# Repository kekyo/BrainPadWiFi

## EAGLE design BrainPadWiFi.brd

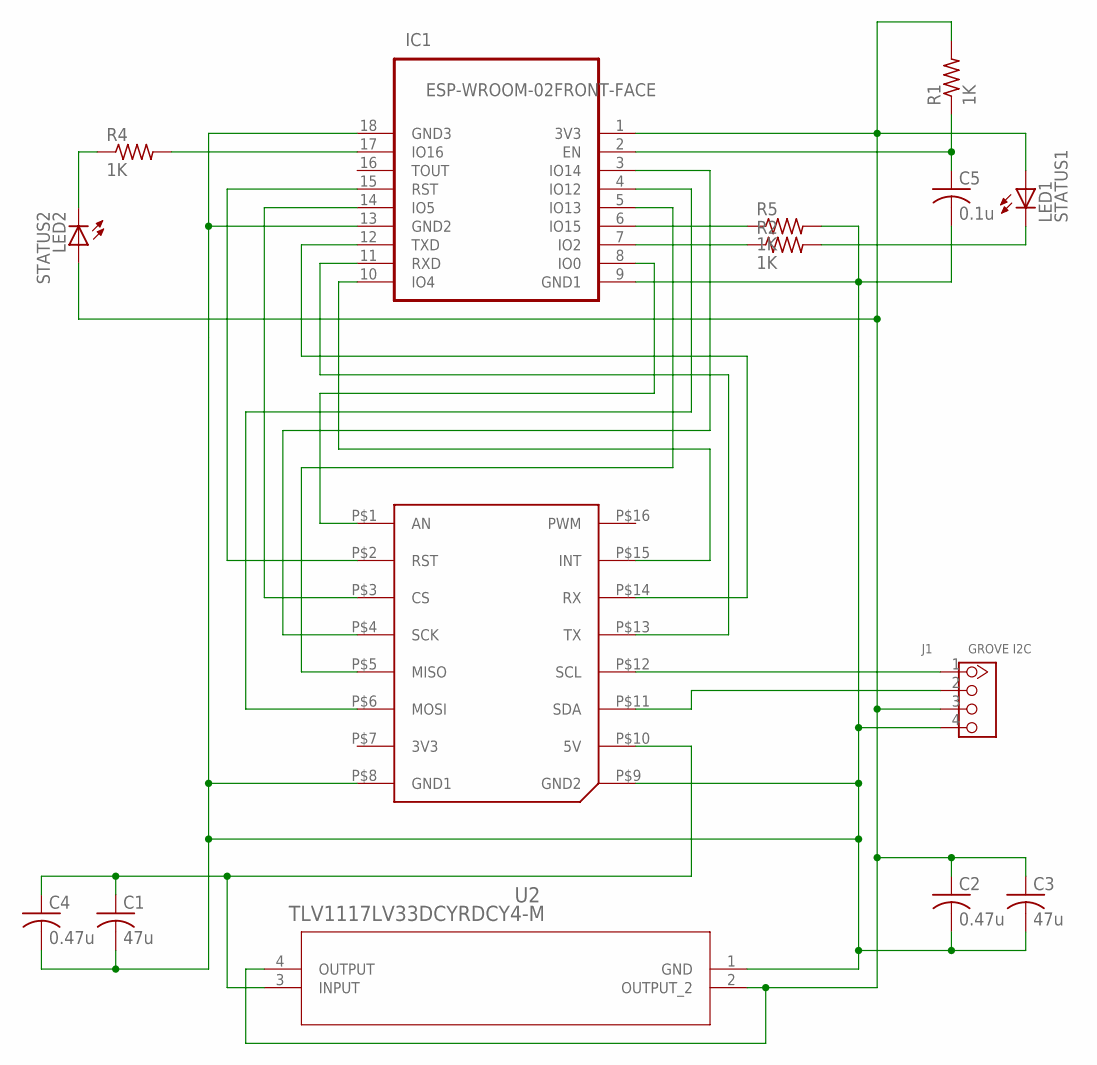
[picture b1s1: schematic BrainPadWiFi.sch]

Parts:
C1, C3: 47u; C1206
C2, C4: 0.47u; C1206
C5: 0.1u; C1206
IC1: ESP-WROOM-02FRONT-FACE; FRONT-FACE
J1: GROVE I2C; HW4-2.0
LED1: STATUS1; SML1206
LED2: STATUS2; SML1206
R1, R2, R4, R5: 1K; R1206
U2: TLV1117LV33DCYRDCY4-M; DCY4-M
U$1: MIKROE_CLICKMINI; MIKROE_BUS_MINI

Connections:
3V3: C2.1, C3.1, IC1.1 (3V3), J1.3, LED1.A, LED2.A, R1.2, U2.2 (OUTPUT_2), U2.4 (OUTPUT)
5V: C1.1, C4.1, U2.3 (INPUT), U$1.P$10 (5V)
CS: IC1.14 (IO5), U$1.P$3 (CS)
EN: C5.1, IC1.2 (EN), R1.1
GND: C1.2, C2.2, C3.2, C4.2, C5.2, IC1.9 (GND1), IC1.13 (GND2), IC1.18 (GND3), J1.4, R5.2, U2.1 (GND), U$1.P$8 (GND1), U$1.P$9 (GND2)
INT: IC1.10 (IO4), U$1.P$15 (INT)
IO2: IC1.7 (IO2), R2.1
IO15: IC1.6 (IO15), R5.1
IO16: IC1.17 (IO16), R4.2
MISO: IC1.5 (IO13), U$1.P$5 (MISO)
MOSI: IC1.4 (IO12), U$1.P$6 (MOSI)
PROG: IC1.8 (IO0), U$1.P$1 (AN)
RST: IC1.15 (RST), U$1.P$2 (RST)
RX: IC1.12 (TXD), U$1.P$14 (RX)
SCK: IC1.3 (IO14), U$1.P$4 (SCK)
SCL: J1.1, U$1.P$12 (SCL)
SDA: J1.2, U$1.P$11 (SDA)
STAT1: LED1.C, R2.2
STAT2: LED2.C, R4.1
TX: IC1.11 (RXD), U$1.P$13 (TX)

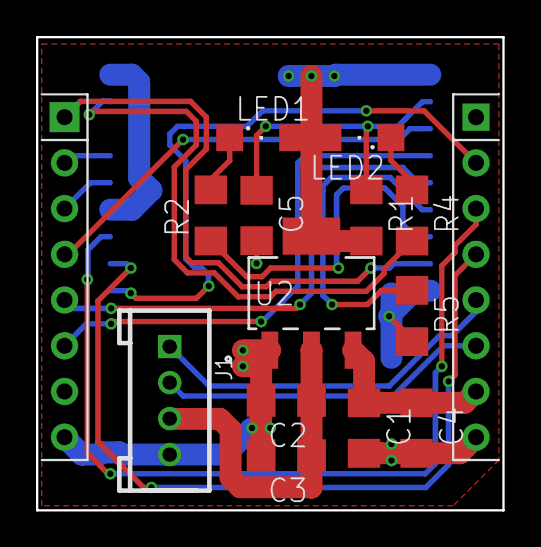
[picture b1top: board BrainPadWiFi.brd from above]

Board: 2 copper layers, 25.9 x 26.3 mm, 16 parts (1 on the bottom side), 20 nets.

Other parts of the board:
U$3: OSH-LOGO

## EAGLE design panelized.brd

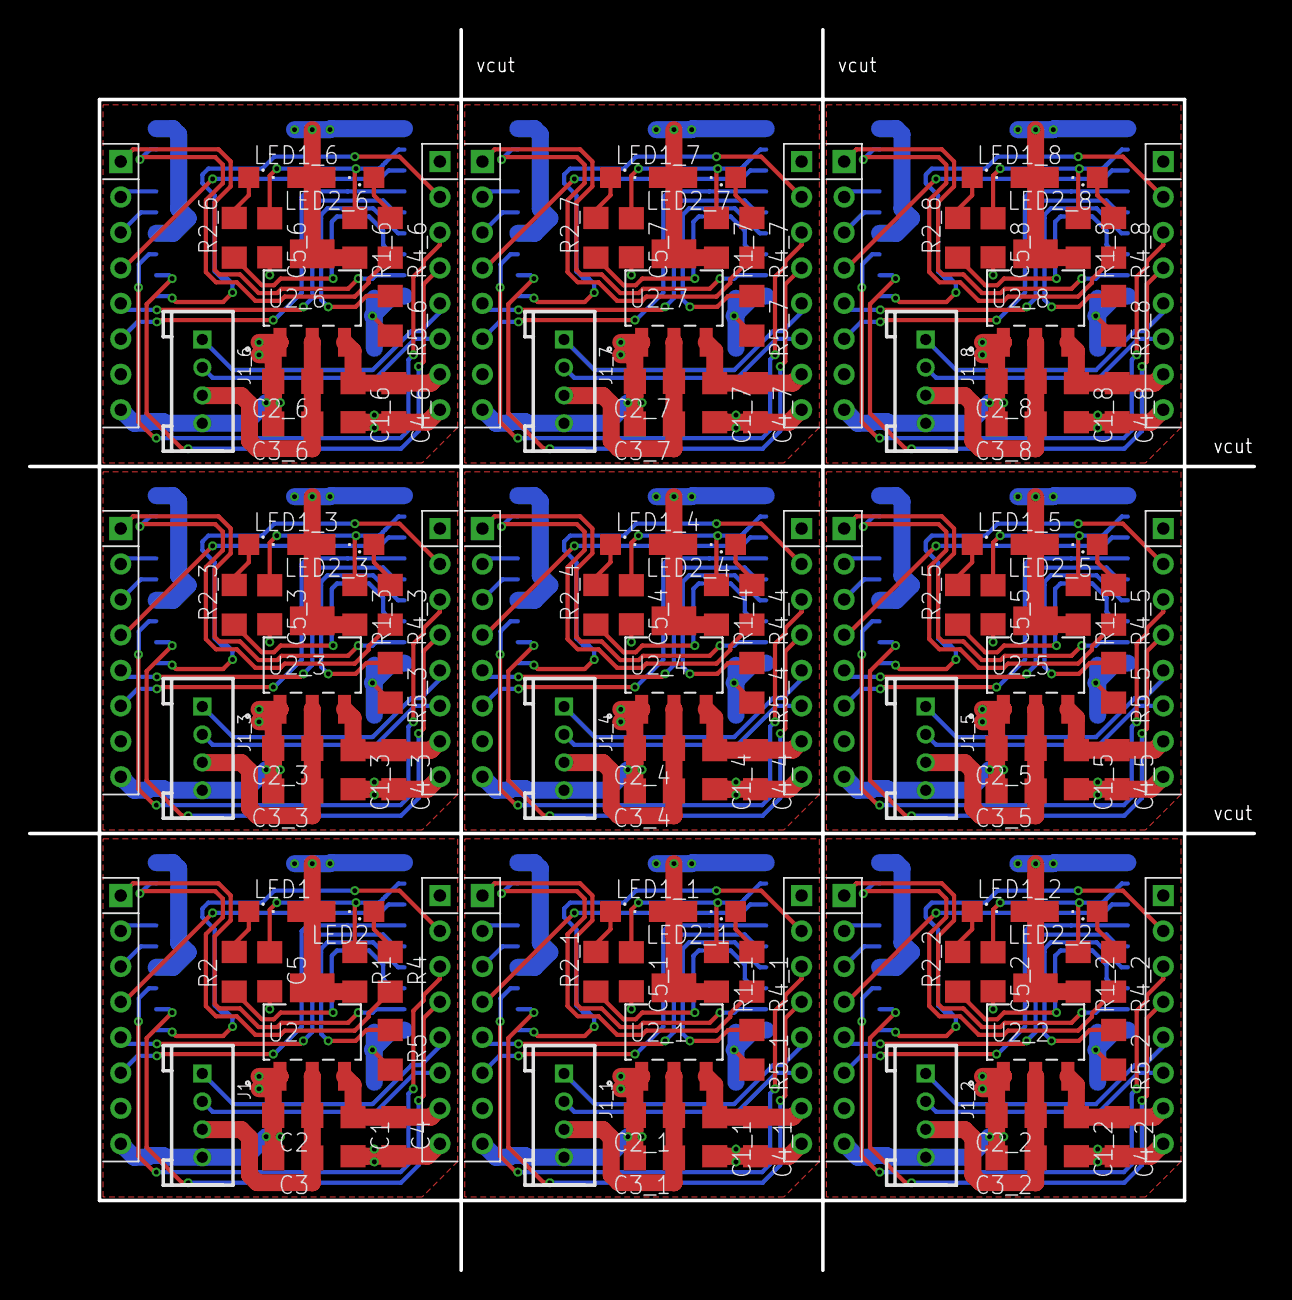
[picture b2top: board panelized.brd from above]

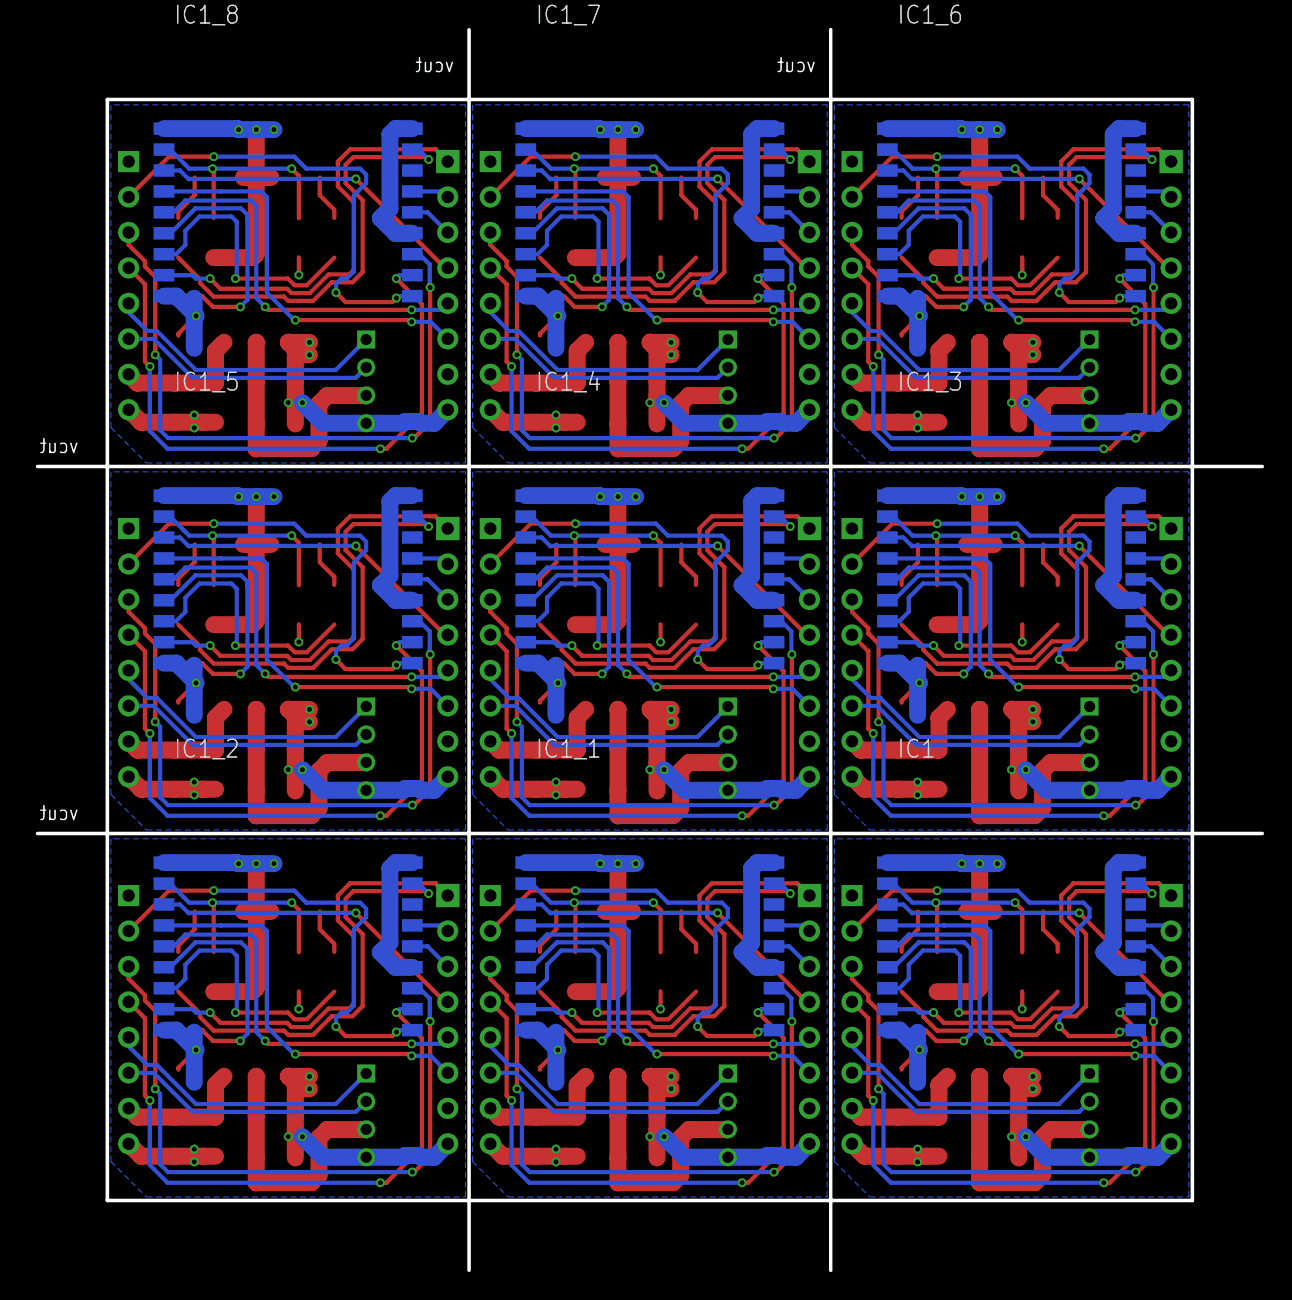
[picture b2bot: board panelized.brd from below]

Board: 2 copper layers, 87.7 x 88.9 mm, 144 parts (9 on the bottom side), 180 nets.

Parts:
C1, C1_1, C1_2, C1_3, C1_4, C1_5, C1_6, C1_7, C1_8, C3, C3_1, C3_2, C3_3, C3_4, C3_5, C3_6, C3_7, C3_8: 47u; C1206
C2, C2_1, C2_2, C2_3, C2_4, C2_5, C2_6, C2_7, C2_8, C4, C4_1, C4_2, C4_3, C4_4, C4_5, C4_6, C4_7, C4_8: 0.47u; C1206
C5, C5_1, C5_2, C5_3, C5_4, C5_5, C5_6, C5_7, C5_8: 0.1u; C1206
IC1, IC1_1, IC1_2, IC1_3, IC1_4, IC1_5, IC1_6, IC1_7, IC1_8: ESP-WROOM-02FRONT-FACE; FRONT-FACE
J1, J1_1, J1_2, J1_3, J1_4, J1_5, J1_6, J1_7, J1_8: GROVE I2C; HW4-2.0
LED1, LED1_1, LED1_2, LED1_3, LED1_4, LED1_5, LED1_6, LED1_7, LED1_8: STATUS1; SML1206
LED2, LED2_1, LED2_2, LED2_3, LED2_4, LED2_5, LED2_6, LED2_7, LED2_8: STATUS2; SML1206
R1, R1_1, R1_2, R1_3, R1_4, R1_5, R1_6, R1_7, R1_8, R2, R2_1, R2_2, R2_3, R2_4, R2_5, R2_6, R2_7, R2_8, R4, R4_1, R4_2, R4_3, R4_4, R4_5, R4_6, R4_7, R4_8, R5, R5_1, R5_2, R5_3, R5_4, R5_5, R5_6, R5_7, R5_8: 1K; R1206
U2, U2_1, U2_2, U2_3, U2_4, U2_5, U2_6, U2_7, U2_8: TLV1117LV33DCYRDCY4-M; DCY4-M
U$1, U$1_1, U$1_2, U$1_3, U$1_4, U$1_5, U$1_6, U$1_7, U$1_8: MIKROE_CLICKMINI; MIKROE_BUS_MINI
U$3, U$3_1, U$3_2, U$3_3, U$3_4, U$3_5, U$3_6, U$3_7, U$3_8: OSH-LOGO

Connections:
3V3: C2.1, C3.1, IC1.1, J1.3, LED1.A, LED2.A, R1.2, U2.2, U2.4
3V3_1: C2_1.1, C3_1.1, IC1_1.1, J1_1.3, LED1_1.A, LED2_1.A, R1_1.2, U2_1.2, U2_1.4
3V3_2: C2_2.1, C3_2.1, IC1_2.1, J1_2.3, LED1_2.A, LED2_2.A, R1_2.2, U2_2.2, U2_2.4
3V3_3: C2_3.1, C3_3.1, IC1_3.1, J1_3.3, LED1_3.A, LED2_3.A, R1_3.2, U2_3.2, U2_3.4
3V3_4: C2_4.1, C3_4.1, IC1_4.1, J1_4.3, LED1_4.A, LED2_4.A, R1_4.2, U2_4.2, U2_4.4
3V3_5: C2_5.1, C3_5.1, IC1_5.1, J1_5.3, LED1_5.A, LED2_5.A, R1_5.2, U2_5.2, U2_5.4
3V3_6: C2_6.1, C3_6.1, IC1_6.1, J1_6.3, LED1_6.A, LED2_6.A, R1_6.2, U2_6.2, U2_6.4
3V3_7: C2_7.1, C3_7.1, IC1_7.1, J1_7.3, LED1_7.A, LED2_7.A, R1_7.2, U2_7.2, U2_7.4
3V3_8: C2_8.1, C3_8.1, IC1_8.1, J1_8.3, LED1_8.A, LED2_8.A, R1_8.2, U2_8.2, U2_8.4
5V: C1.1, C4.1, U2.3, U$1.P$10
5V_1: C1_1.1, C4_1.1, U2_1.3, U$1_1.P$10
5V_2: C1_2.1, C4_2.1, U2_2.3, U$1_2.P$10
5V_3: C1_3.1, C4_3.1, U2_3.3, U$1_3.P$10
5V_4: C1_4.1, C4_4.1, U2_4.3, U$1_4.P$10
5V_5: C1_5.1, C4_5.1, U2_5.3, U$1_5.P$10
5V_6: C1_6.1, C4_6.1, U2_6.3, U$1_6.P$10
5V_7: C1_7.1, C4_7.1, U2_7.3, U$1_7.P$10
5V_8: C1_8.1, C4_8.1, U2_8.3, U$1_8.P$10
CS: IC1.14, U$1.P$3
CS_1: IC1_1.14, U$1_1.P$3
CS_2: IC1_2.14, U$1_2.P$3
CS_3: IC1_3.14, U$1_3.P$3
CS_4: IC1_4.14, U$1_4.P$3
CS_5: IC1_5.14, U$1_5.P$3
CS_6: IC1_6.14, U$1_6.P$3
CS_7: IC1_7.14, U$1_7.P$3
CS_8: IC1_8.14, U$1_8.P$3
EN: C5.1, IC1.2, R1.1
EN_1: C5_1.1, IC1_1.2, R1_1.1
EN_2: C5_2.1, IC1_2.2, R1_2.1
EN_3: C5_3.1, IC1_3.2, R1_3.1
EN_4: C5_4.1, IC1_4.2, R1_4.1
EN_5: C5_5.1, IC1_5.2, R1_5.1
EN_6: C5_6.1, IC1_6.2, R1_6.1
EN_7: C5_7.1, IC1_7.2, R1_7.1
EN_8: C5_8.1, IC1_8.2, R1_8.1
GND: C1.2, C2.2, C3.2, C4.2, C5.2, IC1.9, IC1.13, IC1.18, J1.4, R5.2, U2.1, U$1.P$8, U$1.P$9
GND_1: C1_1.2, C2_1.2, C3_1.2, C4_1.2, C5_1.2, IC1_1.9, IC1_1.13, IC1_1.18, J1_1.4, R5_1.2, U2_1.1, U$1_1.P$8, U$1_1.P$9
GND_2: C1_2.2, C2_2.2, C3_2.2, C4_2.2, C5_2.2, IC1_2.9, IC1_2.13, IC1_2.18, J1_2.4, R5_2.2, U2_2.1, U$1_2.P$8, U$1_2.P$9
GND_3: C1_3.2, C2_3.2, C3_3.2, C4_3.2, C5_3.2, IC1_3.9, IC1_3.13, IC1_3.18, J1_3.4, R5_3.2, U2_3.1, U$1_3.P$8, U$1_3.P$9
GND_4: C1_4.2, C2_4.2, C3_4.2, C4_4.2, C5_4.2, IC1_4.9, IC1_4.13, IC1_4.18, J1_4.4, R5_4.2, U2_4.1, U$1_4.P$8, U$1_4.P$9
GND_5: C1_5.2, C2_5.2, C3_5.2, C4_5.2, C5_5.2, IC1_5.9, IC1_5.13, IC1_5.18, J1_5.4, R5_5.2, U2_5.1, U$1_5.P$8, U$1_5.P$9
GND_6: C1_6.2, C2_6.2, C3_6.2, C4_6.2, C5_6.2, IC1_6.9, IC1_6.13, IC1_6.18, J1_6.4, R5_6.2, U2_6.1, U$1_6.P$8, U$1_6.P$9
GND_7: C1_7.2, C2_7.2, C3_7.2, C4_7.2, C5_7.2, IC1_7.9, IC1_7.13, IC1_7.18, J1_7.4, R5_7.2, U2_7.1, U$1_7.P$8, U$1_7.P$9
GND_8: C1_8.2, C2_8.2, C3_8.2, C4_8.2, C5_8.2, IC1_8.9, IC1_8.13, IC1_8.18, J1_8.4, R5_8.2, U2_8.1, U$1_8.P$8, U$1_8.P$9
INT: IC1.10, U$1.P$15
INT_1: IC1_1.10, U$1_1.P$15
INT_2: IC1_2.10, U$1_2.P$15
INT_3: IC1_3.10, U$1_3.P$15
INT_4: IC1_4.10, U$1_4.P$15
INT_5: IC1_5.10, U$1_5.P$15
INT_6: IC1_6.10, U$1_6.P$15
INT_7: IC1_7.10, U$1_7.P$15
INT_8: IC1_8.10, U$1_8.P$15
IO2: IC1.7, R2.1
IO2_1: IC1_1.7, R2_1.1
IO2_2: IC1_2.7, R2_2.1
IO2_3: IC1_3.7, R2_3.1
IO2_4: IC1_4.7, R2_4.1
IO2_5: IC1_5.7, R2_5.1
IO2_6: IC1_6.7, R2_6.1
IO2_7: IC1_7.7, R2_7.1
IO2_8: IC1_8.7, R2_8.1
IO15: IC1.6, R5.1
IO15_1: IC1_1.6, R5_1.1
IO15_2: IC1_2.6, R5_2.1
IO15_3: IC1_3.6, R5_3.1
IO15_4: IC1_4.6, R5_4.1
IO15_5: IC1_5.6, R5_5.1
IO15_6: IC1_6.6, R5_6.1
IO15_7: IC1_7.6, R5_7.1
IO15_8: IC1_8.6, R5_8.1
IO16: IC1.17, R4.2
IO16_1: IC1_1.17, R4_1.2
IO16_2: IC1_2.17, R4_2.2
IO16_3: IC1_3.17, R4_3.2
IO16_4: IC1_4.17, R4_4.2
IO16_5: IC1_5.17, R4_5.2
IO16_6: IC1_6.17, R4_6.2
IO16_7: IC1_7.17, R4_7.2
IO16_8: IC1_8.17, R4_8.2
MISO: IC1.5, U$1.P$5
MISO_1: IC1_1.5, U$1_1.P$5
MISO_2: IC1_2.5, U$1_2.P$5
MISO_3: IC1_3.5, U$1_3.P$5
MISO_4: IC1_4.5, U$1_4.P$5
MISO_5: IC1_5.5, U$1_5.P$5
MISO_6: IC1_6.5, U$1_6.P$5
MISO_7: IC1_7.5, U$1_7.P$5
MISO_8: IC1_8.5, U$1_8.P$5
MOSI: IC1.4, U$1.P$6
MOSI_1: IC1_1.4, U$1_1.P$6
MOSI_2: IC1_2.4, U$1_2.P$6
MOSI_3: IC1_3.4, U$1_3.P$6
MOSI_4: IC1_4.4, U$1_4.P$6
MOSI_5: IC1_5.4, U$1_5.P$6
MOSI_6: IC1_6.4, U$1_6.P$6
MOSI_7: IC1_7.4, U$1_7.P$6
MOSI_8: IC1_8.4, U$1_8.P$6
PROG: IC1.8, U$1.P$1
PROG_1: IC1_1.8, U$1_1.P$1
PROG_2: IC1_2.8, U$1_2.P$1
PROG_3: IC1_3.8, U$1_3.P$1
PROG_4: IC1_4.8, U$1_4.P$1
PROG_5: IC1_5.8, U$1_5.P$1
PROG_6: IC1_6.8, U$1_6.P$1
PROG_7: IC1_7.8, U$1_7.P$1
PROG_8: IC1_8.8, U$1_8.P$1
RST: IC1.15, U$1.P$2
RST_1: IC1_1.15, U$1_1.P$2
RST_2: IC1_2.15, U$1_2.P$2
RST_3: IC1_3.15, U$1_3.P$2
RST_4: IC1_4.15, U$1_4.P$2
RST_5: IC1_5.15, U$1_5.P$2
RST_6: IC1_6.15, U$1_6.P$2
RST_7: IC1_7.15, U$1_7.P$2
RST_8: IC1_8.15, U$1_8.P$2
RX: IC1.12, U$1.P$14
RX_1: IC1_1.12, U$1_1.P$14
RX_2: IC1_2.12, U$1_2.P$14
RX_3: IC1_3.12, U$1_3.P$14
RX_4: IC1_4.12, U$1_4.P$14
RX_5: IC1_5.12, U$1_5.P$14
RX_6: IC1_6.12, U$1_6.P$14
RX_7: IC1_7.12, U$1_7.P$14
RX_8: IC1_8.12, U$1_8.P$14
SCK: IC1.3, U$1.P$4
SCK_1: IC1_1.3, U$1_1.P$4
SCK_2: IC1_2.3, U$1_2.P$4
SCK_3: IC1_3.3, U$1_3.P$4
SCK_4: IC1_4.3, U$1_4.P$4
SCK_5: IC1_5.3, U$1_5.P$4
SCK_6: IC1_6.3, U$1_6.P$4
SCK_7: IC1_7.3, U$1_7.P$4
SCK_8: IC1_8.3, U$1_8.P$4
SCL: J1.1, U$1.P$12
SCL_1: J1_1.1, U$1_1.P$12
SCL_2: J1_2.1, U$1_2.P$12
SCL_3: J1_3.1, U$1_3.P$12
SCL_4: J1_4.1, U$1_4.P$12
SCL_5: J1_5.1, U$1_5.P$12
SCL_6: J1_6.1, U$1_6.P$12
SCL_7: J1_7.1, U$1_7.P$12
SCL_8: J1_8.1, U$1_8.P$12
SDA: J1.2, U$1.P$11
SDA_1: J1_1.2, U$1_1.P$11
SDA_2: J1_2.2, U$1_2.P$11
SDA_3: J1_3.2, U$1_3.P$11
SDA_4: J1_4.2, U$1_4.P$11
SDA_5: J1_5.2, U$1_5.P$11
SDA_6: J1_6.2, U$1_6.P$11
SDA_7: J1_7.2, U$1_7.P$11
SDA_8: J1_8.2, U$1_8.P$11
STAT1: LED1.C, R2.2
STAT1_1: LED1_1.C, R2_1.2
STAT1_2: LED1_2.C, R2_2.2
STAT1_3: LED1_3.C, R2_3.2
STAT1_4: LED1_4.C, R2_4.2
STAT1_5: LED1_5.C, R2_5.2
STAT1_6: LED1_6.C, R2_6.2
STAT1_7: LED1_7.C, R2_7.2
STAT1_8: LED1_8.C, R2_8.2
STAT2: LED2.C, R4.1
STAT2_1: LED2_1.C, R4_1.1
STAT2_2: LED2_2.C, R4_2.1
STAT2_3: LED2_3.C, R4_3.1
STAT2_4: LED2_4.C, R4_4.1
STAT2_5: LED2_5.C, R4_5.1
STAT2_6: LED2_6.C, R4_6.1
STAT2_7: LED2_7.C, R4_7.1
STAT2_8: LED2_8.C, R4_8.1
TX: IC1.11, U$1.P$13
TX_1: IC1_1.11, U$1_1.P$13
TX_2: IC1_2.11, U$1_2.P$13
TX_3: IC1_3.11, U$1_3.P$13
TX_4: IC1_4.11, U$1_4.P$13
TX_5: IC1_5.11, U$1_5.P$13
TX_6: IC1_6.11, U$1_6.P$13
TX_7: IC1_7.11, U$1_7.P$13
TX_8: IC1_8.11, U$1_8.P$13

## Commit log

2018-09-06 Changed regulator.
2018-09-07 Panelized into 100x100mm for using Fusion PCB minimum PCB service.
2018-09-13 PROG line wired because we grant to an ability for self-programming from BrainPad to ESP.
2018-09-16 Redesigned for next version.
    SMT pieces place only front side. (exclude ESP)
    Add grove connector.
    Registers only 1K.
    Add status2 LED.
2018-09-16 Add grove icon.
2018-09-17 Updated generator rule file (from switch-science) because the official rule file by seeed makes invalid contour wire output.
2018-10-08 Add parts number markers.
2018-10-08 Update images.
